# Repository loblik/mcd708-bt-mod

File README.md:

# mcd708-bt-mod

## Ribbon interconnect pinout

|  1<br/>2 |  3<br/>4  |  5<br/>6  |  7<br/>8  |  9<br/>10  | 11<br/>12 | 13<br/>14 | 15<br/>16 | 17<br/>18 | 19<br/>20 | 21<br/>22 | 23<br/>24 | 25<br/>26 | 27<br/>28 | 29<br/>30 | 31<br/>32 | 33<br/>34 |
|  ---     |     ---   |     ---   |---        |---         |---        |---        |    ---    |---    |---    |---    |---    |---     |---   |---    |---    |---    |
|  GND     |           |           |           |            |   REM     |  ROT-A    |           |       |       |       |       |        |      |       |       |       |
|  GND     |           |    -30V    |    VF1    |    VF2     |  ECO-VCC  |  ECO-PWR  |  ROT-B    |       |       |       |       |        |      |       |       |       |

On female (cable) connector pin 1 is upper leftmost.

## Manuals and datasheets

- MCD708 Service manual <br/>
https://www.manualslib.com/manual/990553/Philips-Mcd708.html

- Display driver <br/>
http://www.princeton.com.tw/Portals/0/Product/PT6311_10.pdf

- Audio processor <br/>
http://www.turuta.md/DSHEETS/PT2314_3.pdf

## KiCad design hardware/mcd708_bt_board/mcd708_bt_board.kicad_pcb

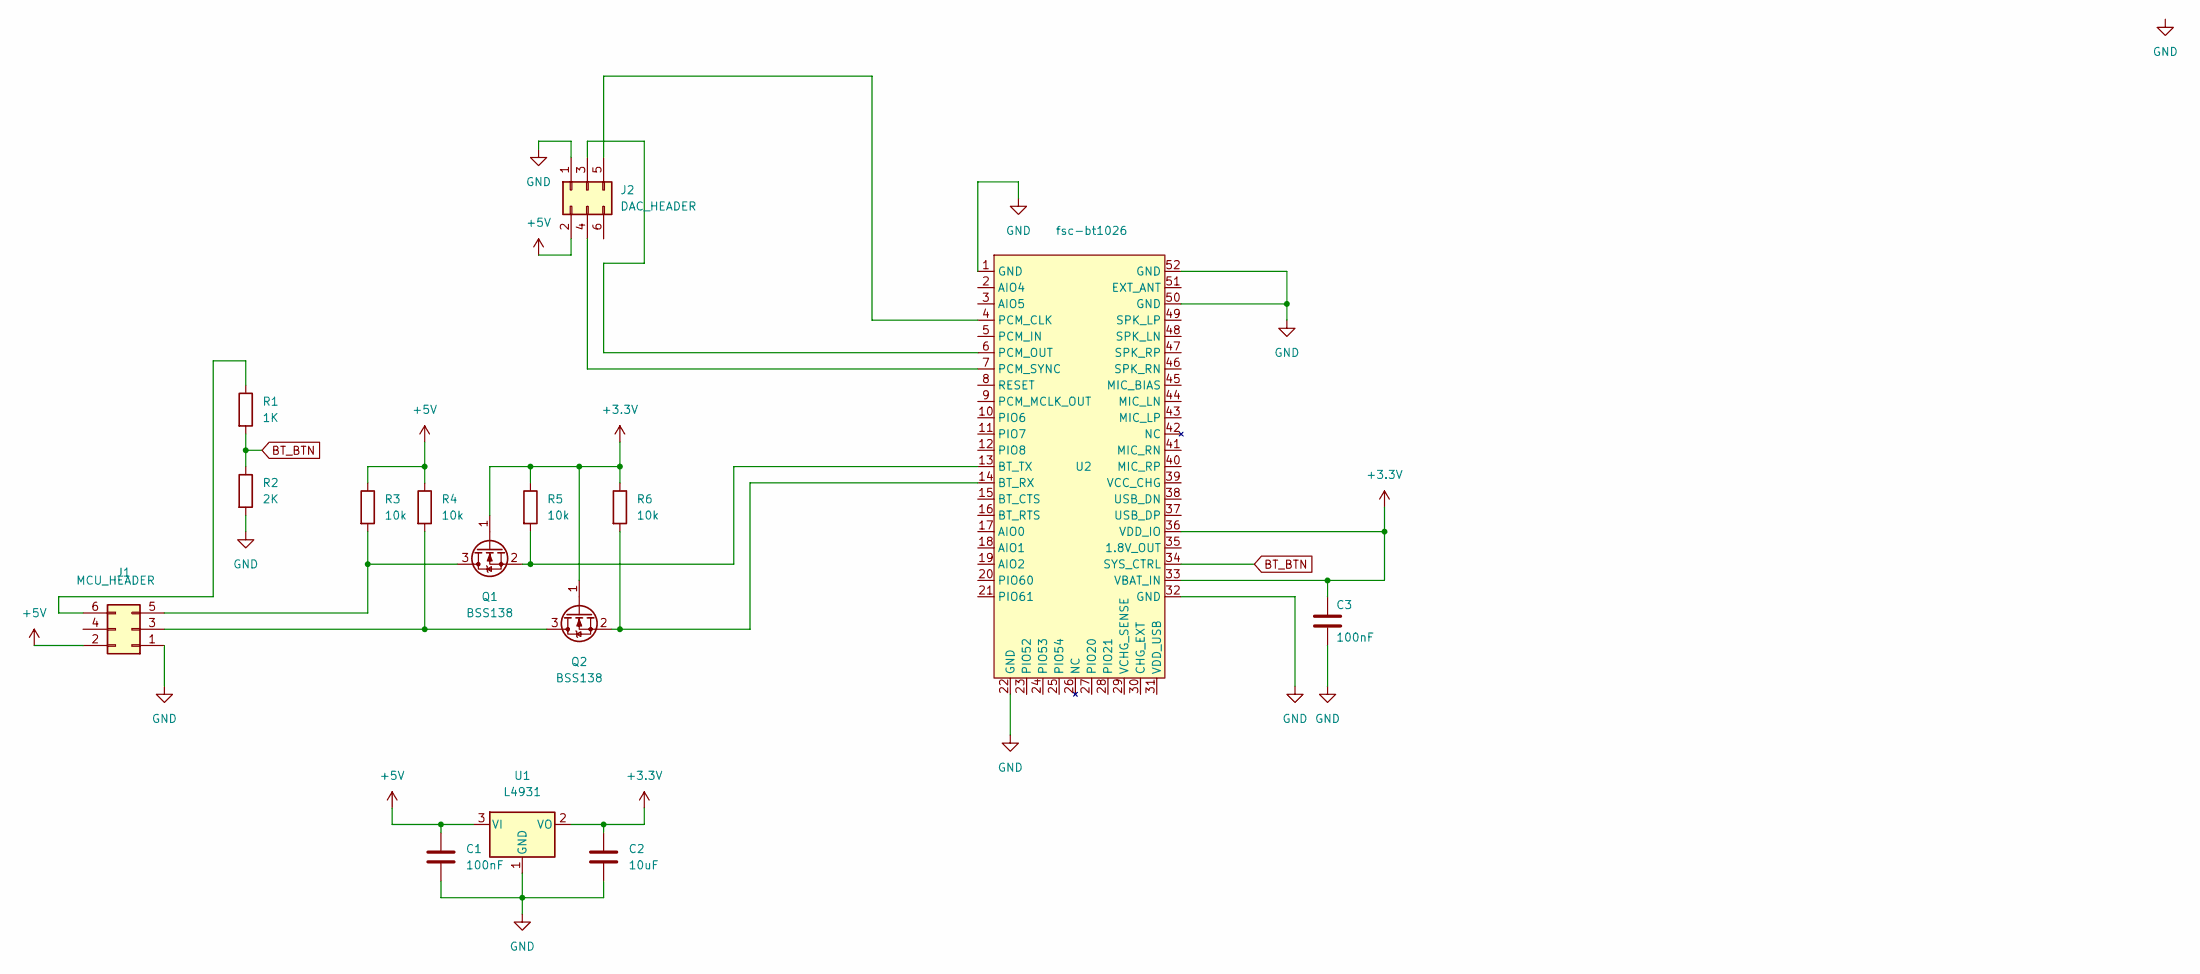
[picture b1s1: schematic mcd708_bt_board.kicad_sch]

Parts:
C1, C3: 100nF; C_Rect_L4.0mm_W2.5mm_P2.50mm
C2: 10uF; CP_Radial_D5.0mm_P2.00mm
J1: MCU_HEADER; IDC-Header_2x03_P2.54mm_Vertical
J2: DAC_HEADER; IDC-Header_2x03_P2.54mm_Vertical
Q1, Q2: BSS138; SOT-23
R1: 1K; R_Axial_DIN0207_L6.3mm_D2.5mm_P7.62mm_Horizontal
R2: 2K; R_Axial_DIN0207_L6.3mm_D2.5mm_P7.62mm_Horizontal
R3, R4, R5, R6: 10k; R_Axial_DIN0207_L6.3mm_D2.5mm_P7.62mm_Horizontal
U1: L4931; TO-252-2
U2: fsc-bt1026; feasycomm

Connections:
+3.3V: C2.1, C3.1, Q1.1 (G), Q2.1 (G), R5.1, R6.1, U1.2 (VO), U2.33 (VBAT_IN), U2.36 (VDD_IO)
+5V: C1.1, J1.2, J2.2, R3.1, R4.1, U1.3 (VI)
BT_BTN: R1.2, R2.1, U2.34 (SYS_CTRL)
GND: C1.2, C2.2, C3.2, J1.1, J2.1, R2.2, U1.1 (GND), U2.1 (GND), U2.22 (GND), U2.32 (GND), U2.50 (GND), U2.52 (GND)
unnamed: Q1.2 (S), R5.2, U2.13 (BT_TX)
unnamed: J1.5, Q1.3 (D), R3.2
unnamed: Q2.2 (S), R6.2, U2.14 (BT_RX)
unnamed: J1.3, Q2.3 (D), R4.2
unnamed: J1.6, R1.1
unnamed: J2.5, U2.4 (PCM_CLK)
unnamed: J2.3, U2.6 (PCM_OUT)
unnamed: J2.4, U2.7 (PCM_SYNC)

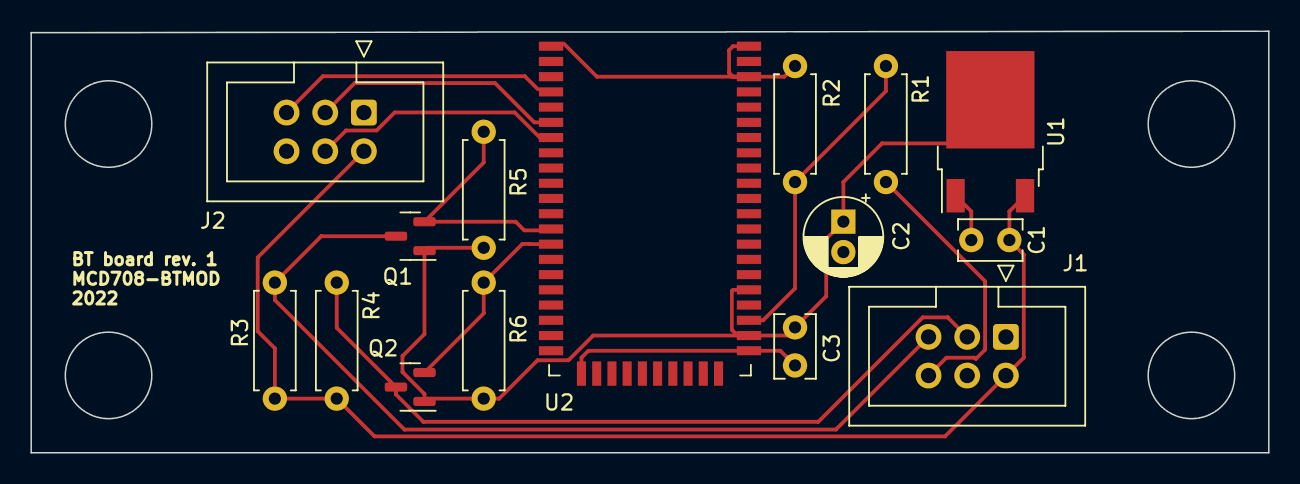
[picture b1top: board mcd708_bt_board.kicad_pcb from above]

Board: 2 copper layers, 81.3 x 27.7 mm, 15 parts (0 on the bottom side), 12 nets.

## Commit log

2023-01-05 add kicad files for bluetooth board
2023-01-05 delete project local file
    Local project setting we probably don't want to be versioned.
2023-01-05 add initial bringup firmware
    1. Simple asynchronous debug output (UART).
    2. Initial implementation of RC-6 state machine.
    RC-5 should follow as remote also sends RC-5 in some cases.
2023-01-05 fix warning in condition
2023-01-05 cleanup main.c
    Only some register names where copied from some uart example. So replace
    the license and do some other cleaning.
2023-01-21 add readme with interconnect pinout
    Interconnect pinout initial version. Added links to datasheets.
2023-01-25 update pinout with VFD supplies
